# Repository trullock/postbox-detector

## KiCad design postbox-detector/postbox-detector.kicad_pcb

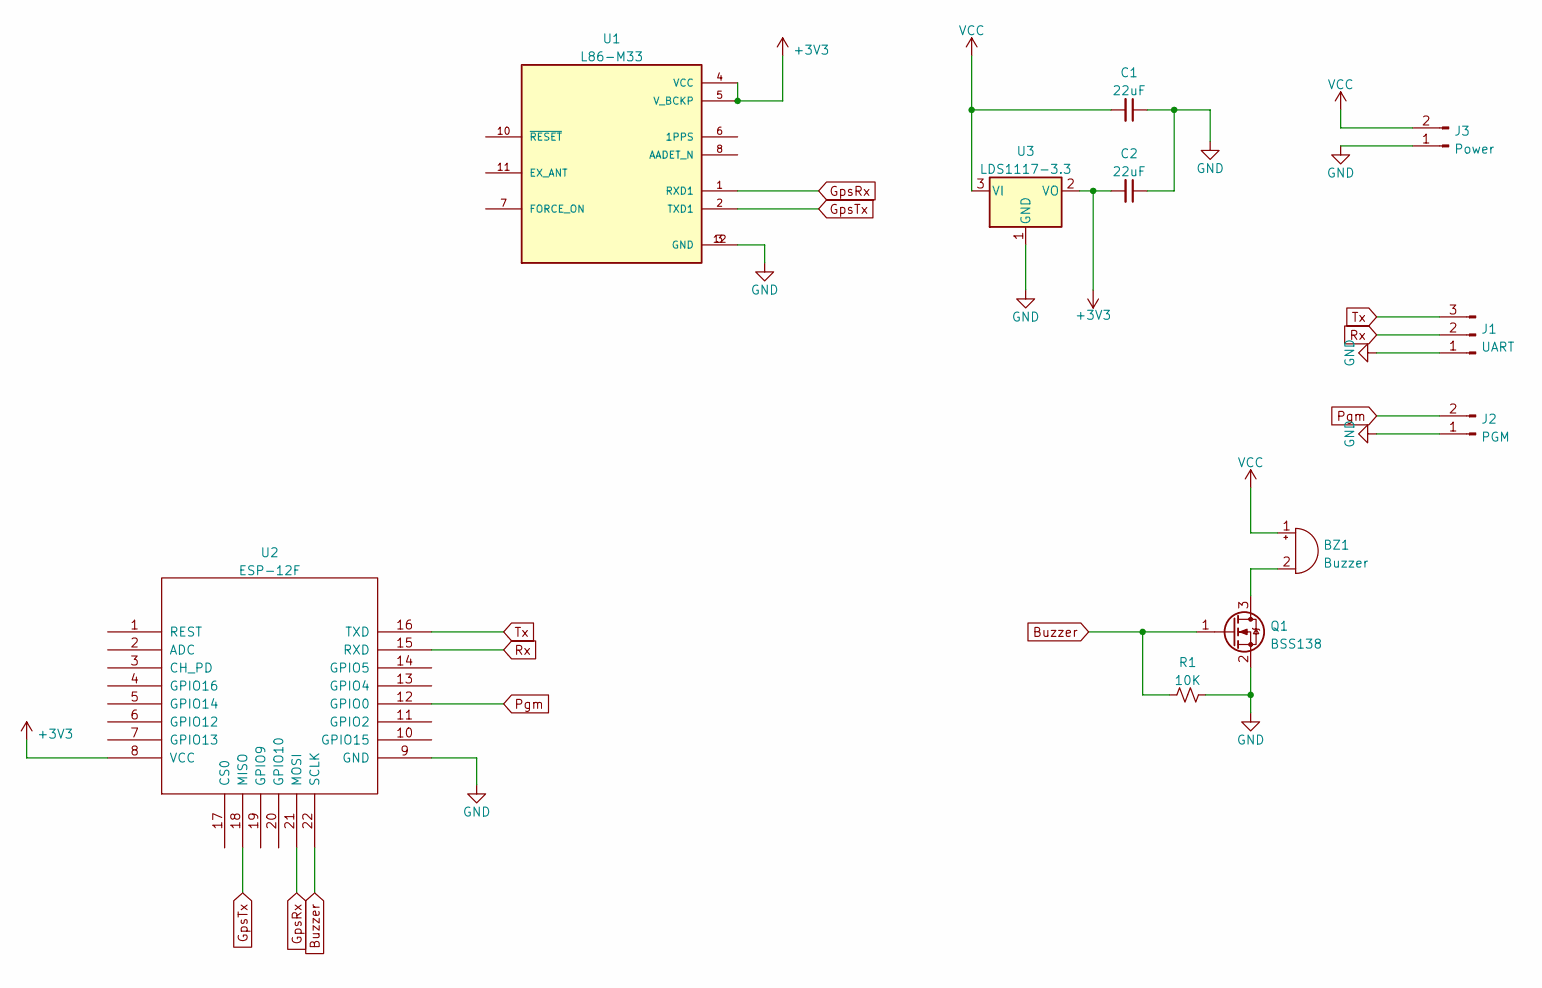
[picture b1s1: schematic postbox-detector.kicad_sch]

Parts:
BZ1: Buzzer; Buzzer_9.2x4.2_WST-0904T
C1, C2: 22uF; C_1206_3216Metric
J1: UART; PinHeader_1x03_P2.54mm_Vertical
J2: PGM; PinHeader_1x02_P2.54mm_Vertical
J3: Power; PinHeader_1x02_P2.54mm_Vertical
Q1: BSS138; SOT-23
R1: 10K; R_1206_3216Metric
U1: L86-M33; XCVR_L86-M33
U2: ESP-12F; ESP-12E
U3: LDS1117-3.3; SOT-223-3_TabPin2

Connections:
+3V3: C2.2, U1.4 (VCC), U1.5 (V_BCKP), U2.8 (VCC), U3.2 (VO)
Buzzer: Q1.1 (G), R1.2, U2.22 (SCLK)
GND: C1.1, C2.1, J1.1, J2.1, J3.1, Q1.2 (S), R1.1, U1.3 (GND), U1.12 (GND), U2.9 (GND), U3.1 (GND)
GpsRx: U1.1 (RXD1), U2.21 (MOSI)
GpsTx: U1.2 (TXD1), U2.18 (MISO)
unnamed: BZ1.2 (+), Q1.3 (D)
Pgm: J2.2, U2.12 (GPIO0)
Rx: J1.2, U2.15 (RXD)
Tx: J1.3, U2.16 (TXD)
VCC: BZ1.1 (-), C1.2, J3.2, U3.3 (VI)

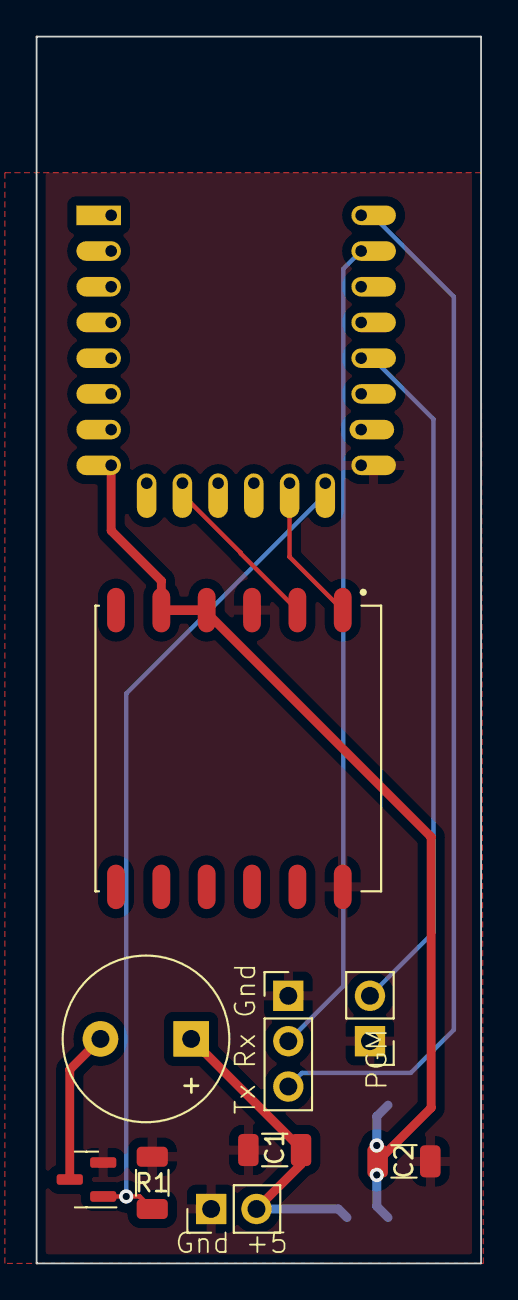
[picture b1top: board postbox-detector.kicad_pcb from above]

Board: 2 copper layers, 24.9 x 68.7 mm, 11 parts (1 on the bottom side), 10 nets.

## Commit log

2023-12-06 started adding pcb
2023-12-06 crude test implementation and pcb layout
